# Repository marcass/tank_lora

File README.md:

# tank_lora
Meaure water tank levels with and send signal with LoRa radio on on private network with alerts

## Hardware overview
Using an ATMega brain, a lora radio implemented by AI Thinker, an ultrasonic distance measuring device and powering with solar we will send signal from remote locations to a hub and publish water levels to a web accessable platform
* 6-2.7V power rail to supply
   * LoRa module (on board Buck converts to 3.3v for supplying radio and ATMega chip)
 * 3.3V rail to supply everything (avoiding 5V)

### Power
6V, 3W solar panel to supply power rail (2.75 to 6V) with storage that will have at least a battery and possibly a supercap. Conservaton stratagies include:
* Using a TPL5010 as a watchdog timer
   * Sends a wake pulse that can be programmed to be up to every 2hrs by varying resistance to Prog pin
   * Needs a 'done' pulse sent from MCU at least 20ms prior to next wake pulse or it will send a reset to MCU
   * Savings on changing fuses for watchdog and brownout detection are not of great benefit. Doing this would save some power (see page 397 in http://www.atmel.com/Images/Atmel-7766-8-bit-AVR-ATmega16U4-32U4_Datasheet.pdf )
      * 0.5microA in power down mode with WDT disabled vs 6microA with WDT enabled
* Disabling DC-DC converter (uses ~35microA)
   *  Would need to use somthing like a latching transistor circuit for TPL5010 to trigger, like http://m.eet.com/media/1151168/24527-112300di.pdf, then MCU feeds the TPL5010 the done pulse prior to shutting down
      * This would mean we can't power TPL5010 from LoRa module 3.3v rail causing it to use 43nA at 5v
   * counclusion: Just put LoRa radio and MCU to sleep adn allow TPL5010 to manage brownout as it operates as low as 1.8v

#### Battery protection
Low voltage protection provided by https://electronics.stackexchange.com/questions/148586/to-protect-a-lipo-cell-from-undervoltage-how-low-current-is-low-enough (top of page circuit)

Overvoltage protection provided by solar charger like adafruuit solar charger

### Parts
* Lora radios with ATMega32u4 https://www.aliexpress.com/item/5PCS-lot-LoRa32u4-RA-02-433M-Lora-Wireless-WIFI-Module-Long-Range-communication-1KM-LiPo-Atmega328/32812205344.html?spm=2114.13010608.0.0.r6qCKR
   * Similar to adafruit feather LoRa https://learn.adafruit.com/adafruit-feather-32u4-radio-with-lora-radio-module/power-management
   * Better range than nRF
* Charging circuit from 6V 3W panel https://www.aliexpress.com/item/MCP73871-PowerBoost-USB-5V-DC-Solar-Lipoly-Lithium-Lon-Polymer-Charger-Board-3-7V-4-2V/32795379739.html?spm=2114.13010208.99999999.264.vDACyf
   * Similar to MPTT charge circuit
* Solar panels https://www.aliexpress.com/item/Solar-Panel-Module-for-Light-Battery-Cell-Phone-Charger-Portable-6V-2W-330MA-DIY/32408341015.html?spm=2114.13010608.0.0.j91m7t
* 3.3V Ultrasound range detection
* TPL5010 for watchdog timer http://www.ti.com/lit/ds/symlink/tpl5010.pdf
   * 35nA at 2.8v

## Software overview

Program LoRa board with onboard ATMega32u4 chip with arduino IDE

### Flashing

* Change nodeID on each sketch prior to Flashing
* Flash remote stations with 'sensor_node'
* Flash nodes that are only forwarders duplex_forwarder (specifying which nodes can be forwarded), or duplex_all_forwarder if you are forwarding all signal, or sensor_duplex if taking readings off a tank too. Alter prefix of forwarder for tracking if necessary
* Node attached to base station (Rpi) flashed with master node

### Libraries
* NewPing http://playground.arduino.cc/Code/NewPing (NewPing not working with 3.3V range detectors so using custom script)
   * Can also use measure echo pin pulse using a while loop or PulseIn builtin
* LoRa http://www.arduinolibraries.info/libraries/lo-ra

## Lora gateway
* Using an esp32 based board with lora radio on it
* send data via restful api over https
* https://github.com/marcass/api

## Testing

# Notes
LoRa32u4 module has connection:

Radio module | ATMega32u4 arduino pin
--- | ---
NSS |   1 or 8
RST |   4
DIO0 | 7 (PE6) https://www.arduino.cc/en/Hacking/PinMapping32u4  

These need to be set in LoRa.setPins(ss, reset, dio0); (see https://github.com/sandeepmistry/arduino-LoRa/blob/master/API.md)

# Power consumption
* Battery protection circuit:
   * 28uA when circuit above voltage?
   * 0.6uA when curcuit below voltage
* Battery testing circuit = 0uA
* LoRa module is flaky when voltages < 2.80 (when on external watcdog) supplied to 5V pin, otherwise works well.
* LoRa module uses ~387microA when in power down sleep mode
* Solar charger uses 26uA as quiescent current
* Totoal consumption with led resistor removed from LoRa32u4 is 1.2mA on assembled board. (4 predicted, but still OK)

NOTE: TPL 5010 with ~90k Ohm resistor gives 26min between wakes

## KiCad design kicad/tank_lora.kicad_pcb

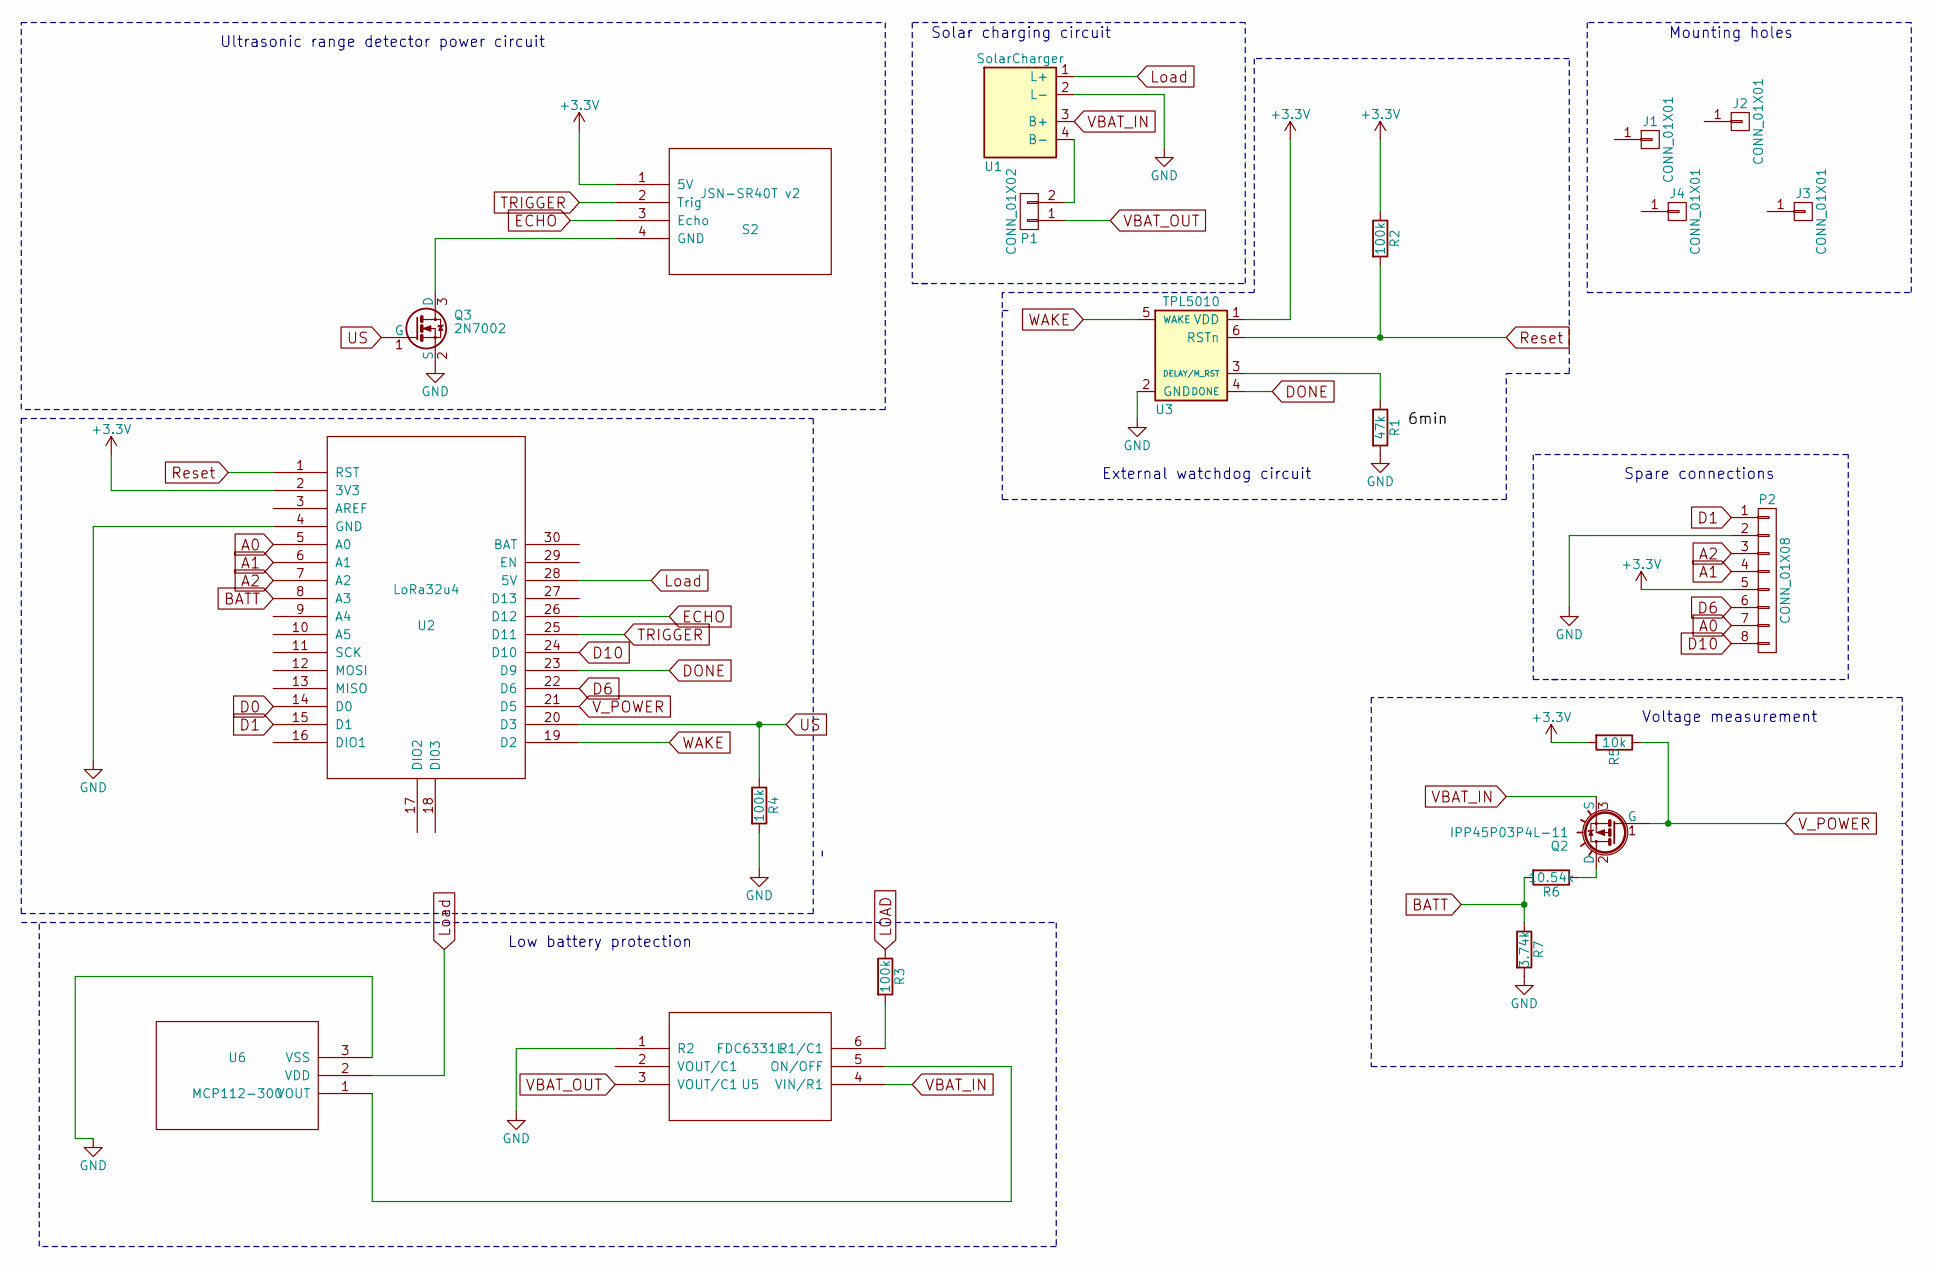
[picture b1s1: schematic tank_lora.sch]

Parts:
J1, J2, J3, J4: CONN_01X01; MountingHole_3.2mm_M3_DIN965_Pad
P1: CONN_01X02; JST_PH_B2B-PH-K_02x2.00mm_Straight
P2: CONN_01X08; PhoenixContact_MCV-G_08x5.08mm_Vertical
Q2: IPP45P03P4L-11; TO-220_Neutral123_Vertical
Q3: 2N7002; TSOT-23
R1: 47k; Resistor_SMD+THTuniversal_0805to1206_RM10_HandSoldering
R2, R3, R4: 100k; Resistor_SMD+THTuniversal_0805to1206_RM10_HandSoldering
R5: 10k; Resistor_SMD+THTuniversal_0805to1206_RM10_HandSoldering
R6: 10.54k; Resistor_SMD+THTuniversal_0805to1206_RM10_HandSoldering
R7: 3.74k; Resistor_SMD+THTuniversal_0805to1206_RM10_HandSoldering
S2: JSN-SR40T v2; JSN-SR04T
U1: SolarCharger; Solar_charger
U2: LoRa32u4
U3: TPL5010; SOT-23-6_Handsoldering
U5: FDC6331L; TSOT-6-MK06A_Handsoldering
U6: MCP112-300; TO-92_Inline_Wide

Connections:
+3V3: P2.5, R2.1, R5.2, S2.1 (5V), U2.2 (3V3), U3.1 (VDD)
A0: P2.7, U2.5 (A0)
A1: P2.4, U2.6 (A1)
A2: P2.3, U2.7 (A2)
BATT: R6.2, R7.1, U2.8 (A3)
D0: U2.14 (D0)
D1: P2.1, U2.15 (D1)
D6: P2.6, U2.22 (D6)
D10: P2.8, U2.24 (D10)
DONE: U2.23 (D9), U3.4 (DONE)
ECHO: S2.3 (Echo), U2.26 (D12)
GND: P2.2, Q3.2 (S), R1.2, R4.2, R7.2, U1.2 (L-), U2.4 (GND), U3.2 (GND), U5.1 (R2), U6.3 (VSS)
LOAD: R3.1, U1.1 (L+), U2.28 (5V), U6.2 (VDD)
unnamed: P1.2, U1.4 (B-)
unnamed: Q2.2 (D), R6.1
unnamed: Q3.3 (D), S2.4 (GND)
unnamed: R1.1, U3.3 (DELAY/M_RST)
unnamed: R3.2, U5.6 (R1/C1)
unnamed: U5.5 (ON/OFF), U6.1 (VOUT)
Reset: R2.2, U2.1 (RST), U3.6 (RSTn)
TRIGGER: S2.2 (Trig), U2.25 (D11)
US: Q3.1 (G), R4.1, U2.20 (D3)
VBAT_IN: Q2.3 (S), U1.3 (B+), U5.4 (VIN/R1)
VBAT_OUT: P1.1, U5.3 (VOUT/C1)
V_POWER: Q2.1 (G), R5.1, U2.21 (D5)
WAKE: U2.19 (D2), U3.5 (WAKE)

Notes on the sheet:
Voltage measurement
Low battery protection
External watchdog circuit
Solar charging circuit
Ultrasonic range detector power circuit
Mounting holes
Spare connections

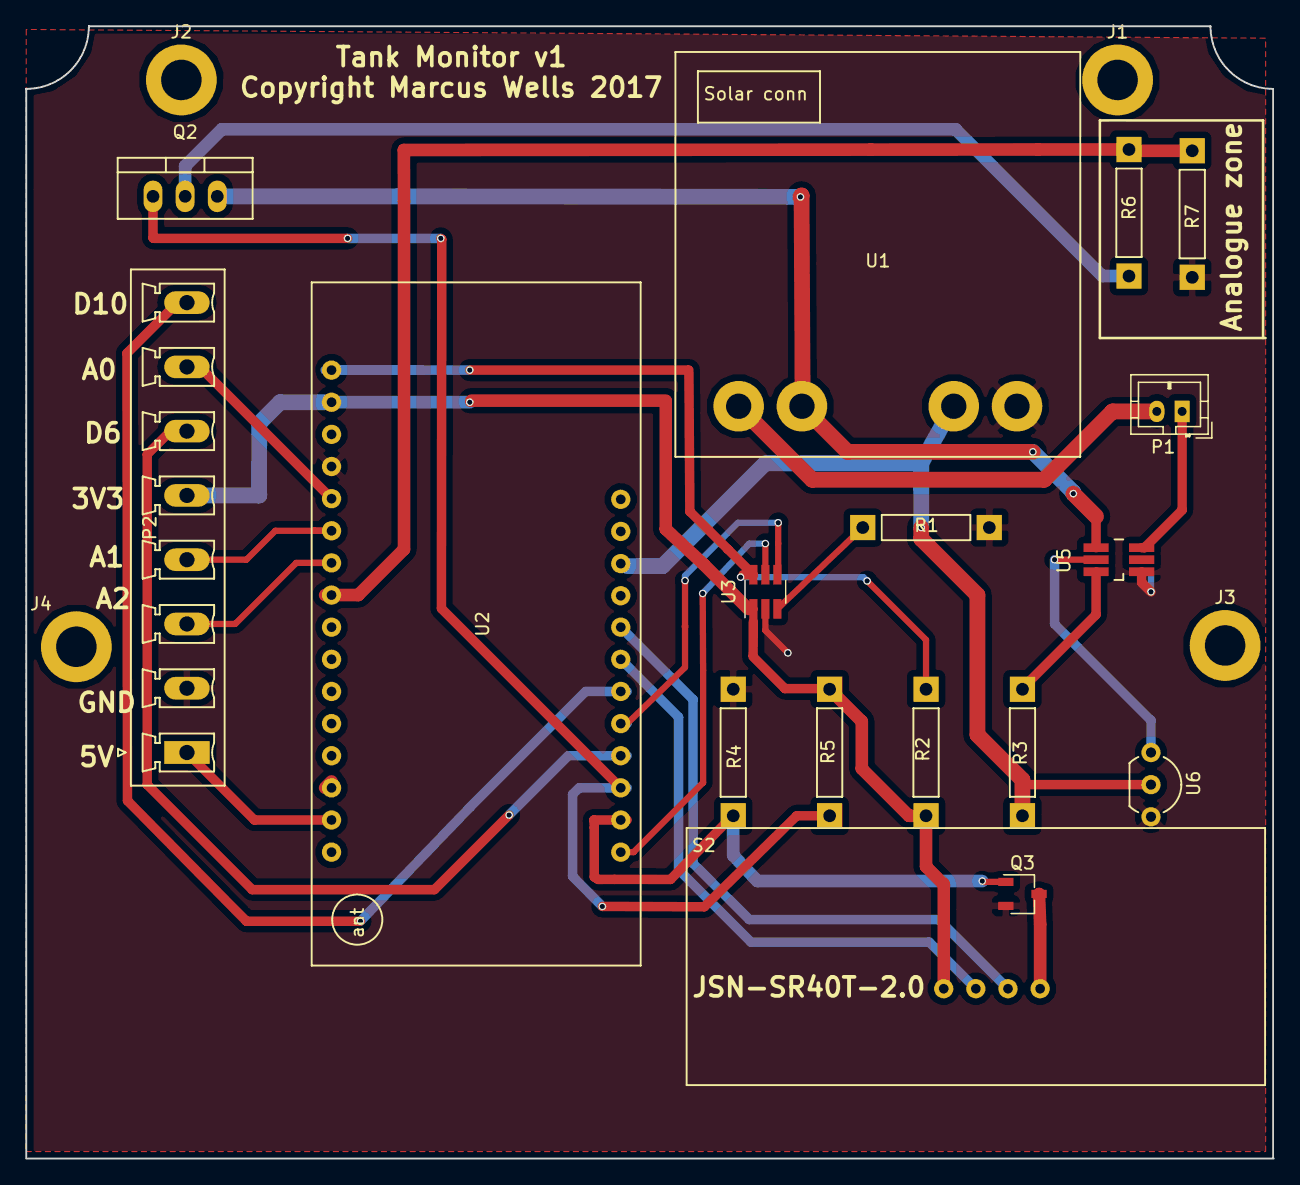
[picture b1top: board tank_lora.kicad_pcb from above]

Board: 2 copper layers, 98.6 x 89.5 mm, 21 parts (0 on the bottom side), 25 nets.

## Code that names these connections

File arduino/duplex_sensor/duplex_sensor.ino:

/* TODO
 *  set list of allowed nodes for forwarding
 *  test
 */  


#include <SPI.h>
#include <LoRa.h>
//Sonar stuff
//sleep stuff http://www.engblaze.com/hush-little-microprocessor-avr-and-arduino-sleep-mode-basics/
#include <avr/interrupt.h>
#include <avr/power.h>
#include <avr/sleep.h>
#include <avr/io.h>

//debug
#define debug

int counter = 0;
/*Assign node numbers
 * 1. Top tank
 * 2. Noels break
 * 2. Sal's bush
 */
const int NODE_ID = 1;
//allowed to forward for sals - more verstile than using syncword
int allowed_senders [] = {}//declare allowed address values here

#define SS 1                 //NSS pin def for lora lib
#define V_PIN  0             //measure voltage off this pin
#define POWER  3             //Power up n-channel mosfet to read distance
#define RESET  4             //RESET pin for lora radio
#define V_POWER 5            //pull down p-channel mosfet to measure voltage
#define DIO  7               //DIO 0  for lora lib
#define TRIGPIN  11          // Arduino pin tied to trigger pin on the ultrasonic sensor.
#define ECHOPIN     12       // Arduino pin tied to echo pin on the ultrasonic sensor.


float voltage;
unsigned long send_timer;
const unsigned long SEND_THRESH = 1500000; //25min

//LoRa radio setup https://github.com/sandeepmistry/arduino-LoRa/blob/master/API.md
//Lower number if closer receiver (saves power)
//LoRa.setTxPower(txPower); //Supported values are between 2 and 17 for PA_OUTPUT_PA_BOOST_PIN, 0 and 14 for PA_OUTPUT_RFO_PIN.

void setup() {
  send_timer = millis();
  //disable sleep bit:
  sleep_disable();
  pinMode(DONE, OUTPUT);
  digitalWrite(DONE, LOW);
  pinMode(POWER, OUTPUT);
  digitalWrite(POWER, LOW);
  pinMode(V_POWER, OUTPUT);
  digitalWrite(V_POWER, HIGH);
  //ultrasonic pins
  pinMode(ECHOPIN, INPUT_PULLUP);
  pinMode(TRIGPIN, OUTPUT);
 
  #ifdef debug
    Serial.begin(9600);
    while (!Serial); //uncomment to require serial connection to work
    Serial.println("LoRa Sender");
  #endif
  
  LoRa.setPins(SS, RESET, DIO); 
  if (!LoRa.begin(433E6)) { // initialise at 433MHz
    #ifdef debug
      Serial.println("Starting LoRa failed!");
    #endif
    while (1);
  }
  //.setup analog ref for battery testing
  analogReference(INTERNAL); //measures at 1.1V ref to give a value for flaoting voltage form batt

}

//battery testing function
//A3 connected to voltage divider form battery, this is turned on by D0
// see http://fettricks.blogspot.co.nz/2014/01/reducing-voltage-divider-load-to-extend.html
void batteryMeasure() {
  digitalWrite(POWER, LOW);//close mosfet to measure
  delayMicroseconds(20); //wait for cap to discharge before reading
  //Serial.print("Value of measure pin is: ");
  int val = analogRead(V_measurePin); //measure analog val for conversion
  //Serial.println(val);
  digitalWrite(POWER, HIGH);//open mosfet to conserve power
  //convert. Returns actual voltage, ie 3.768 = 3.768V
  voltage = (((float)val / 442) * 1.1) / (1.1 / 4.2);
}

//measrue distance to water
void distMeasure(){
  digitalWrite(POWER, HIGH);
  delay(350); //measured as nneding to be above 280ms for saturation of boost converter
  digitalWrite(TRIGPIN, LOW); // Set the trigger pin to low for 2uS
  delayMicroseconds(2);
  digitalWrite(TRIGPIN, HIGH); // Send a 10uS high to trigger ranging
  delayMicroseconds(10);
  digitalWrite(TRIGPIN, LOW); // Send pin low again
  int distance = pulseIn(ECHOPIN, HIGH,26000); // Read in times pulse
  distance= distance/58;
  #ifdef debug
    Serial.print(distance);
    Serial.println("   cm");                    
  #endif
}

void onReceive(int packetSize) {
  if (packetSize == 0) return;          // if there's no packet, return

  // read packet header bytes:
  byte sender = LoRa.read();            // sender address

  String incoming = "";

  while (LoRa.available()) {
    incoming += (char)LoRa.read();
  }

  // if the recipient isn't this device or broadcast,
  if (sender != 0xFF) {
    #ifdef debug
      Serial.println("This message is not for me.");
    #endif
    return;                             // skip rest of function
  }

  //forward the packet
  LoRa.beginPacket();
  LoRa.print(incoming);
  LoRa.endPacket();

  #ifdef debug
    // if message is for this device, or broadcast, print details:
    Serial.println("Received from: 0x" + String(sender, HEX));
    Serial.println("Message: " + incoming);
    Serial.println("RSSI: " + String(LoRa.packetRssi()));
    Serial.println("Snr: " + String(LoRa.packetSnr()));
    Serial.println();
  #endif
}

void send_local_data(){
  batteryMeasure();
  distMeasure();
  //send packet
  LoRa.beginPacket();
  LoRa.print("PY:");//tag for serial listner
  LoRa.print(NODE_ID);
  LoRa.print(";");
  LoRa.print(dist);
  LoRa.print(";");
  LoRa.print(voltage);
  LoRa.print(";");
  LoRa.endPacket();
}


void loop() {
  //send local data now and then
  if (millis() - send_timer > SEND_THRESH) {
    send_local_data();
    send_timer = millis();
  }

  // parse for a packet, and call onReceive with the result:
  onReceive(LoRa.parsePacket());
}

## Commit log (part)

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2017-06-19 kicad initialisation
2017-06-20 furhter kicad updates
2017-07-02 started arduino stuff
2017-07-03 reverse engineered NSS RST pin connection to get radio working
2017-07-03 updated pin mapping in sketch and docs, not recieving
2017-07-04 added lib for LoRa32u4
2017-07-04 more power stuff
2017-07-04 aligned sketch with schematic
2017-07-04 continual readm updates....
2017-07-06 update schematic for MOSFET and begin pin setting for sleep in sketch
2017-07-08 added libs, updated schematic
2017-07-09 started pcb layout
2017-07-11 pyton listner
2017-07-11 more python updates
2017-07-11 python message handling
2017-07-12 python maths....
2017-07-12 python update for serial read - check to see if it is not blooking on serial read
2017-07-14 struggling with queues
2017-07-14 updated python
2017-07-15 started logging stuff
2017-07-15 started alert app bot
2017-07-15 added gitignore
2017-07-16 setup alert bot
2017-07-17 pigration
2017-07-18 lets try this
2017-07-18 some changes to paths
2017-07-18 more fruitless fiddling
2017-07-18 optimising for pi
2017-07-19 refinements for errors
2017-07-19 refining...
2017-07-19 rrd stuff
2017-07-19 fixed many bugs. many more to go. rrd plotting now working. replying to status requests in the most verbose way possible
2017-07-20 separated classes, got callback buttons working (largely)
2017-07-20 more fiddling with graphs
2017-07-20 graphs work, help menu sucks
2017-07-20 working bot and graphs
2017-07-20 added furhter exclusion
2017-07-20 fiddling
2017-07-21 refine testing
2017-07-21 sorting rrd stuff
2017-07-21 added batteries to rrd
2017-07-21 rrd prblem when running as systemd process fixed (i think)
2017-07-22 datastore fun
2017-07-22 component changes
2017-07-22 refineing bot
2017-07-22 changed step val
2017-07-22 tests updated
2017-07-22 test for tpl updated further
2017-07-23 area graphs!
2017-07-23 updated battery alert value
2017-07-23 testing scripts for components
2017-07-24 updated schmeatic with mosfet model
2017-07-24 updated some glitches in sketch
2017-07-24 pcb update
2017-07-25 sleep tests
2017-07-26 updated pcb with test info
2017-07-26 ultrasound test
2017-07-27 pcb...
2017-07-27 the turd continues to be polished
2017-07-29 production ready
2017-07-31 updated bot, need to test
2017-08-01 more alert stuff
2017-08-01 moving files to working machine
2017-08-01 improved bot
2017-08-02 polishing
2017-08-02 turd polsihing
2017-08-02 more bot improvements
2017-08-02 mod the rrd update for logging purposes
2017-08-03 button formatting
2017-08-03 test data mod
2017-08-03 handling mulitple chats on alerts
2017-08-03 sorted messasge handling bug
2017-08-06 sqllite plotting
2017-08-06 batt test
2017-08-07 switching from rrd to matplotlib and sqllite
2017-08-07 repairing changes
2017-08-07 plotting
2017-08-07 sorted v2 sensor
2017-08-08 plot testing
2017-08-08 fiddling with readable dates
2017-08-09 time display fluffing
2017-08-10 duplex forwarder/sensor added and polished alerts
2017-08-10 dumped rrd, polished alerts
2017-08-10 tidying repo
2017-08-10 fixed url message
2017-08-10 colour updated and title fixed
2017-08-11 tested duplex handling
2017-08-14 testing...
2017-08-14 more testing
2017-08-15 udev rules added and tidied arduino stuff
2017-08-15 exception handling for serial port
2017-08-16 handling erroneous values
2017-08-16 not sure but something
2017-08-17 turd polishing
2017-08-17 us testing
2017-08-17 tidied
2017-08-20 updated for error values
2017-08-20 sketch updated for calibration with internal ref for chip variation
2017-08-20 autossh setup
2017-08-20 updated resistor value
2017-08-22 amalgamated
2017-08-22 temperature sensing
2017-08-23 added partitiioned python files for ease of reading
2017-08-23 ddploy duplex
2017-08-23 plotting refining
2017-08-23 editing
2017-08-24 tested
2017-08-24 ongoing fludd
2017-08-24 moving stuff
2017-08-24 tidying arduino code
2017-08-24 changed timer and node
2017-08-24 timings...
2017-08-25 message fixed
2017-08-26 updated board remvoing 5V rail
2017-08-29 test receiver update
2017-08-31 adjusted for volumes
2017-08-31 tanks alteration
2017-08-31 sketch adjustments
2017-08-31 updated tank measurements
2017-08-31 nmerging
2017-08-31 function call reationailsation
2017-08-31 status flag handling made global
2017-08-31 still debugging
2017-09-01 fixed status message
2017-09-02 updated for persistence and status handling
2017-09-02 updated duplex
2017-09-02 sorted status persistence and remved battery alert plot
2017-09-04 updated for batt status
2017-09-04 plot adjustments
2017-09-04 added batt status reset abilities
2017-09-04 fixed errors
2017-09-05 updated for error in db fetch
2017-09-12 altered plots to remove ticks
2017-09-27 filtering progress
2017-09-28 filtered data in group plot
2017-11-17 fixed med plotting
2017-11-19 changed boundary values on batt voltage
2017-11-19 error handling
2018-05-10 refactor of code for api
2018-05-11 started to fragment files
2018-05-17 simplyfying
2018-05-17 avoiding circular imports
2018-05-18 cleaning up for dry run before dummy data insertion
2018-05-20 sorted sql foreign key syntax, started on making junk data
2018-05-20 sorted changing status on data sort
2018-05-21 started to sort through plot.py
2018-05-22 lunch calling
2018-05-22 rejigging telegram
2018-05-23 working alert system
2018-05-23 working on falsk
2018-05-24 updating flask app
2018-05-24 alerts working in test mode with tidyup for flask app
2018-05-24 working flask api (auth tested)
2018-05-24 added tank adding to api
2018-05-25 started spa
2018-05-25 fidddling with app
2018-05-25 working on spa
2018-05-26 refining spa
2018-05-26 so slow.....
2018-05-27 made it pretty
2018-05-27 tidied and added user update
2018-05-27 need to place message in login fail
2018-05-28 redirects working
2018-05-28 reresh token madness
2018-05-28 rereshing wroking with orig token (bad)
2018-05-29 fucking around with hosting
2018-05-29 chomod of socket
2018-05-29 got website working manually now need to do systemd
2018-05-29 updated uwsgi ing
2018-05-30 error ironed out, now get uwsgi working at boot (fuck)
2018-05-30 needed ini file after all
2018-06-01 MOre messages for use of spa
2018-06-05 deploying for production
2018-06-05 not finding port, testing... again
2018-06-05 not finding port, testing... again,,
2018-06-05 problems found, i think
2018-06-07 working in production now
2018-06-08 updated dodgy config
2018-06-08 working now
2018-06-11 tidy up
2018-07-06 basis for speeding up datetime parsing
2018-08-30 circular buffer and median filtering
2018-09-01 posting to influx
2018-09-01 debug push
2018-09-01 got rid of import
2018-09-01 serial fucking with me
2018-09-01 token problems or threads?
2018-09-01 blocking serial. using threads
2018-09-01 stopped the exceptions
2018-09-01 not sure
2018-09-02 change batt level to a float
2018-09-10 removed lib
2019-02-01 updated docker file
2019-02-01 converted to python 3
2019-02-01 working on docker now
2019-02-01 docker is not apssing through ussable serial port
2019-02-01 finally have a serial port in container
2019-02-02 fixed utossh file for future use and arranged systemd files
2019-03-01 getting somewhere with data ingress and oled
2019-03-03 clenaing up for the advent of no pi
2019-03-03 got it graphing at least
2019-03-04 removed serial prints, tidied up display
2019-03-05 working receiver
2019-03-29 added wifi reconnect conditional statement
2019-08-10 updated readme to remove rpi stuff
2019-11-02 Bump mixin-deep from 1.3.1 to 1.3.2 in /tank_monitor
    Bumps [mixin-deep](https://github.com/jonschlinkert/mixin-deep) from 1.3.1 to 1.3.2.
    - [Release notes](https://github.com/jonschlinkert/mixin-deep/releases)
    - [Commits](https://github.com/jonschlinkert/mixin-deep/compare/1.3.1...1.3.2)
2019-12-28 debugging receivers
2019-12-28 Bump webpack-bundle-analyzer from 2.13.1 to 3.3.2 in /tank_monitor
    Bumps [webpack-bundle-analyzer](https://github.com/webpack-contrib/webpack-bundle-analyzer) from 2.13.1 to 3.3.2.
    - [Release notes](https://github.com/webpack-contrib/webpack-bundle-analyzer/releases)
    - [Changelog](https://github.com/webpack-contrib/webpack-bundle-analyzer/blob/master/CHANGELOG.md)
    - [Commits](https://github.com/webpack-contrib/webpack-bundle-analyzer/compare/v2.13.1...v3.3.2)
2019-12-28 Bump webpack-dev-server from 2.11.2 to 3.1.11 in /tank_monitor
    Bumps [webpack-dev-server](https://github.com/webpack/webpack-dev-server) from 2.11.2 to 3.1.11.
    - [Release notes](https://github.com/webpack/webpack-dev-server/releases)
    - [Changelog](https://github.com/webpack/webpack-dev-server/blob/master/CHANGELOG.md)
    - [Commits](https://github.com/webpack/webpack-dev-server/compare/v2.11.2...v3.1.11)
2019-12-28 Bump lodash from 4.17.10 to 4.17.15 in /tank_monitor
    Bumps [lodash](https://github.com/lodash/lodash) from 4.17.10 to 4.17.15.
    - [Release notes](https://github.com/lodash/lodash/releases)
    - [Commits](https://github.com/lodash/lodash/compare/4.17.10...4.17.15)
2019-12-28 more data and checked out forwarder script
2019-12-29 getting http post working
2019-12-29 added debugging to http for 4to6
2019-12-30 changed some pin assignments
2020-06-06 Bump websocket-extensions from 0.1.3 to 0.1.4 in /tank_monitor
    Bumps [websocket-extensions](https://github.com/faye/websocket-extensions-node) from 0.1.3 to 0.1.4.
    - [Release notes](https://github.com/faye/websocket-extensions-node/releases)
    - [Changelog](https://github.com/faye/websocket-extensions-node/blob/master/CHANGELOG.md)
    - [Commits](https://github.com/faye/websocket-extensions-node/compare/0.1.3...0.1.4)
2020-07-16 Bump lodash from 4.17.10 to 4.17.19 in /tank_monitor
    Bumps [lodash](https://github.com/lodash/lodash) from 4.17.10 to 4.17.19.
    - [Release notes](https://github.com/lodash/lodash/releases)
    - [Commits](https://github.com/lodash/lodash/compare/4.17.10...4.17.19)
2020-09-05 Bump http-proxy from 1.17.0 to 1.18.1 in /tank_monitor
    Bumps [http-proxy](https://github.com/http-party/node-http-proxy) from 1.17.0 to 1.18.1.
    - [Release notes](https://github.com/http-party/node-http-proxy/releases)
    - [Changelog](https://github.com/http-party/node-http-proxy/blob/master/CHANGELOG.md)
    - [Commits](https://github.com/http-party/node-http-proxy/compare/1.17.0...1.18.1)
2020-12-21 Bump node-notifier from 5.2.1 to 8.0.1 in /tank_monitor
    Bumps [node-notifier](https://github.com/mikaelbr/node-notifier) from 5.2.1 to 8.0.1.
    - [Release notes](https://github.com/mikaelbr/node-notifier/releases)
    - [Changelog](https://github.com/mikaelbr/node-notifier/blob/v8.0.1/CHANGELOG.md)
    - [Commits](https://github.com/mikaelbr/node-notifier/compare/v5.2.1...v8.0.1)
2021-03-08 Bump elliptic from 6.4.0 to 6.5.4 in /tank_monitor
    Bumps [elliptic](https://github.com/indutny/elliptic) from 6.4.0 to 6.5.4.
    - [Release notes](https://github.com/indutny/elliptic/releases)
    - [Commits](https://github.com/indutny/elliptic/compare/v6.4.0...v6.5.4)
2021-03-29 Bump y18n from 3.2.1 to 3.2.2 in /tank_monitor
    Bumps [y18n](https://github.com/yargs/y18n) from 3.2.1 to 3.2.2.
    - [Release notes](https://github.com/yargs/y18n/releases)
    - [Changelog](https://github.com/yargs/y18n/blob/master/CHANGELOG.md)
    - [Commits](https://github.com/yargs/y18n/commits)
2021-05-07 Bump lodash from 4.17.10 to 4.17.21 in /tank_monitor
    Bumps [lodash](https://github.com/lodash/lodash) from 4.17.10 to 4.17.21.
    - [Release notes](https://github.com/lodash/lodash/releases)
    - [Commits](https://github.com/lodash/lodash/compare/4.17.10...4.17.21)
2021-05-09 Bump hosted-git-info from 2.6.0 to 2.8.9 in /tank_monitor
    Bumps [hosted-git-info](https://github.com/npm/hosted-git-info) from 2.6.0 to 2.8.9.
    - [Release notes](https://github.com/npm/hosted-git-info/releases)
    - [Changelog](https://github.com/npm/hosted-git-info/blob/v2.8.9/CHANGELOG.md)
    - [Commits](https://github.com/npm/hosted-git-info/compare/v2.6.0...v2.8.9)
2021-06-28 updated cert
2021-06-30 working config in testing esp32
2021-07-25 preparing for merge

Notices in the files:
kicad/tank_lora.kicad_pcb:
Copyright Marcus Wells 2017
